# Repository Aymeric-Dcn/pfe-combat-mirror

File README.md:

# PFE Combat Mirror — boxer motion capture

*[Version française](README.fr.md)*

Final-year project at Polytech Montpellier (MEA), with the Biomedical Engineering department of CSULB, the Australian company [Combat Mirror](https://combatmirror.com/) and LAAS-CNRS (Gepetto team).

**Goal:** fit a boxing mirror with pressure sensors (impact strength and location), synchronize them with the boxer's joint kinematics measured by RGB cameras with [RT-COSMIK](https://github.com/Gepetto/rt-cosmik), then score the training session with a learned model (Transformer).

| Deliverable | Status (2026-11-20) |
|---|---|
| 1. RT-COSMIK setup | **Done.** Full pipeline with one webcam (detection, skeleton, biomechanical model, joint angles to CSV); real time at 30 fps on the Polytech Debian machine |
| 2. Mirror instrumentation | **In progress.** 4-sensor FlexiForce force plate prototype: corner module (3D), conditioning (schematic, simulations, breadboard-validated), Nucleo firmware and PC script working; sensors on order |
| 3. Synchronization + CSV | **In progress.** Camera side ready; force plate frames carry a 2 kHz sample counter; hardware camera trigger planned (Nucleo TIM1) |
| 4. Data processing (ML) | Not started |

The progress report (French, LaTeX + compiled PDF) is in [`docs/rapport/`](docs/rapport/).

## Layout

```
config/cam_params/intrinsics/   webcam calibration (format read by RT-COSMIK main)
rtcosmik/patches/               our changes to RT-COSMIK (git apply)
scripts/tests/                  webcam, YOLO engine, NLF skeleton, engine header checks
scripts/calibration/            intrinsic calibration (checkerboard on a screen) + recompute
scripts/analysis/               take quality check + skeleton overlay video
scripts/tools/                  RT-COSMIK main setup + export from the container
scripts/forceplate/             force plate acquisition, live view and calibration (PC)
docker/                         image built on top of cosmik-dev-container's
results/                        takes (csv, plots; videos stay out of git)
hardware/3d/                    force plate parts (OpenSCAD): corner module, 4-sensor test rig
hardware/simulation/            sensor conditioning simulation (ngspice)
hardware/electronics/           sensor conditioning schematic (KiCad)
hardware/firmware/              Nucleo F072RB acquisition firmware (4 sensors, 2 kHz)
docs/                           setup guide (EN/FR), progress report and calibration protocol (FR)
```

## Quick start

Environment: the Docker image from [cosmik-dev-container](https://github.com/MaximeSabbah/cosmik-dev-container) (CUDA 12.1, Ubuntu 22.04, ROS 2 Humble, torch 2.4.1) plus Gepetto's RT-COSMIK `main`. Full setup, Windows/WSL 2 notes and troubleshooting: [`docs/SETUP.md`](docs/SETUP.md).

```bash
# inside the container
git clone https://github.com/Aymeric-Dcn/pfe-combat-mirror.git /root/pfe-combat-mirror
bash /root/pfe-combat-mirror/scripts/tools/setup_rtcosmik_main.sh
cd ~/workspace/ros_ws/RT-COSMIK-main
export YOLO_VERBOSE=False
python3 scripts/python/core/run_pipeline.py --online --cameras 0
```

Stand still and fully visible until `Model calibration finished`, then press `q` and `Ctrl+C` to stop. Results go to `output/<no_trial>/`.

On a recorded take:

```bash
python3 /root/pfe-combat-mirror/scripts/analysis/analyze_take.py output/demo_03
bash    /root/pfe-combat-mirror/scripts/analysis/overlay_offsets.sh output/demo_03 "0 0.5 1 1.5 2"
```

## Force plate (prototype)

Four FlexiForce A201 sensors, one under each corner of a plate, give the impact force (sum) and location (centre of pressure).

```
FlexiForce -> op-amp conditioning (MCP6004, 3.3 V) -> RC filter 480 Hz -> Nucleo F072RB ADC (2 kHz) -> USB -> forceplate.py
```

| Part | Where |
|---|---|
| Corner module and 300 mm test rig (OpenSCAD, parametric) | [`hardware/3d/`](hardware/3d/) |
| Conditioning schematic (KiCad) and bench test sheets | [`hardware/electronics/`](hardware/electronics/) |
| Circuit simulations (ngspice) | [`hardware/simulation/`](hardware/simulation/) |
| Acquisition firmware (STM32CubeIDE, register level) | [`hardware/firmware/nucleo_acq/`](hardware/firmware/nucleo_acq/) |
| PC acquisition, live view and calibration | [`scripts/forceplate/`](scripts/forceplate/) |
| Calibration protocol (FR) | [`docs/protocole_etalonnage.md`](docs/protocole_etalonnage.md) |

Quick start: import `hardware/firmware/nucleo_acq` in STM32CubeIDE and flash it (Run), then:

```bash
pip install pyserial numpy matplotlib
cd scripts/forceplate
python forceplate.py -p COM4 monitor     # or /dev/ttyACM0; --sim to try without the board
python forceplate.py -p COM4 live
```

## Changes to RT-COSMIK

- `0001-nlf-import-torchvision.patch`: the NLF TorchScript model calls `torchvision::nms`, which is only registered once `torchvision` is imported. Without it the pipeline process crashes at startup.
- `0002-settings-single-webcam.patch`: 640x480 at 30 fps, one camera, `sbs` inverse kinematics, subject height and weight.

## References

- RT-COSMIK: https://github.com/Gepetto/rt-cosmik
- Camera calibration (LAAS): https://github.com/Gepetto/cams_calibration
- ROS 2 bridge: https://github.com/Gepetto/rtcosmik_ros
- Dev container: https://github.com/MaximeSabbah/cosmik-dev-container

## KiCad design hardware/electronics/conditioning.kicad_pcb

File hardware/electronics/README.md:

# Conditioning board (rev 3.1): 4-channel shield for the NUCLEO-F072RB

KiCad 10 project `conditioning`.
One MCP6004 conditions the 4 FlexiForce A201 sensors (V_OUT = V_REF x (1 + R_F / R_sensor)); the board plugs on the Arduino headers of the Nucleo.

## Connectors

| Ref | Function | Footprint |
|---|---|---|
| FS1-FS4 | FlexiForce sensors, plugged directly (outer pins active, centre pin unused) | 1x03 female socket, 2.54 mm |
| J1 | Nucleo CN6 (power): 3V3 and GND used | 1x08 male header |
| J2 | Nucleo CN8 (analog): A0-A3 sensors, A4 V_REF | 1x06 male header |
| J3 | Nucleo CN9 (digital): D7/PA8 camera trigger, D6/PB10 camera strobe; D0/D1 (ST-LINK UART) left free | 1x08 male header |
| J4 | Cameras: 1 trigger, 2 strobe, 3 GND | 1x03 male header |
| JP1 | Mode: 1-2 sensitive (1.03 V), 3-4 standard (0.51 V), 5-6 high force (0.10 V) | 2x03 header + jumper |
| JP2 | 3V3 from the Nucleo; remove the jumper to measure the current | 1x02 header + jumper |
| JP3-JP6 | Op-amp output to the RO/CO filter; remove to drive the filter from a generator | 1x02 header + jumper |

## Test points

Single header pins (1x01).

| Ref | Signal |
|---|---|
| TP1-TP4 | op-amp outputs (before RO) |
| TP5-TP8 | ADC inputs (after the RO/CO filter) |
| TP9 | V_REF |
| TP10 | 3V3 |
| TP11-TP14 | GND, one near each channel for the probe clips |

No test point on the inverting inputs: a probe there adds about 100 pF and makes the amplifier ring.

## Shield placement

The male headers are inserted from the component side and soldered on the copper side, so the board works single-sided.
Header positions, from the Arduino Uno R3 layout (pin centres, mm, origin on A0, x to the right, y towards the digital headers):

| Header | Pin 1 | Last pin | y |
|---|---|---|---|
| J2 (CN8) | A0: x = 0 | A5: x = 12.70 | 0 |
| J1 (CN6) | NC: x = -22.86 | VIN: x = -5.08 | 0 |
| J3 (CN9) | D0: x = 15.24 | D7: x = -2.54 | 48.26 |

Check these positions before etching: place the KiCad footprint `Module:Arduino_UNO_R3` on the PCB as a reference, or measure the Nucleo headers.

Height: the Nucleo with the shield fits between the plates of the test rig (47.75 mm gap); orient the corner modules so that the sensor tails point to the centre.

## Etching rules (Polytech machine, provisional)

Single-sided, no plated holes: tracks 0.6 mm minimum, clearance 0.5 mm, pads 2 mm minimum (2.5 mm for headers), 1.0 mm drills for headers, 0.8 mm for resistors and capacitors. To be confirmed with the technician.

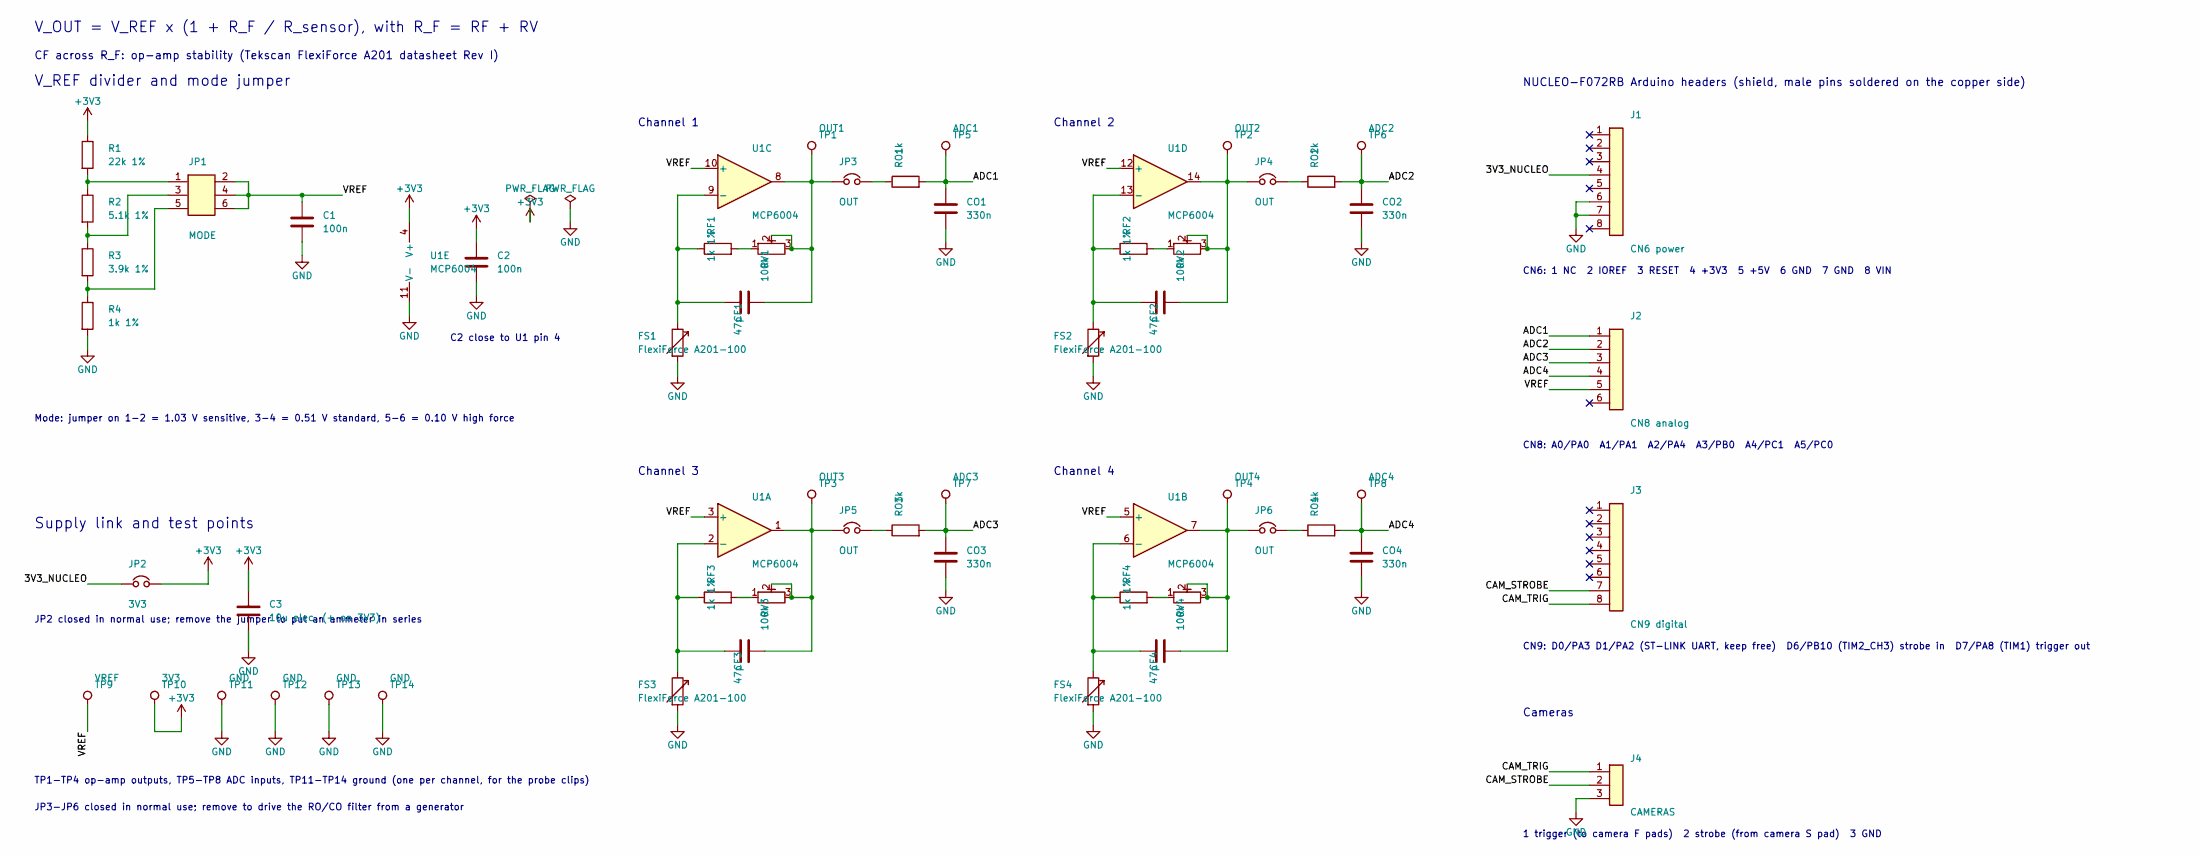
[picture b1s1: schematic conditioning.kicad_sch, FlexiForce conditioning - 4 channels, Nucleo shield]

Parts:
C1, C2: 100n; C_Disc_D5.0mm_W2.5mm_P2.50mm
C3: 10u elec. (+ on 3V3); CP_Radial_D5.0mm_P2.50mm
CF1, CF2, CF3, CF4: 47p; C_Disc_D5.0mm_W2.5mm_P2.50mm
CO1, CO2, CO3, CO4: 330n; C_Disc_D5.0mm_W2.5mm_P2.50mm
FS1, FS2, FS3, FS4: FlexiForce A201-100; PinSocket_1x03_P2.54mm_Vertical
J1: CN6 power; PinHeader_1x08_P2.54mm_Vertical
J2: CN8 analog; PinHeader_1x06_P2.54mm_Vertical
J3: CN9 digital; PinHeader_1x08_P2.54mm_Vertical
J4: CAMERAS; PinHeader_1x03_P2.54mm_Vertical
JP1: MODE; PinHeader_2x03_P2.54mm_Vertical
JP2: 3V3; PinHeader_1x02_P2.54mm_Vertical
JP3, JP4, JP5, JP6: OUT; PinHeader_1x02_P2.54mm_Vertical
R1: 22k 1%; R_Axial_DIN0207_L6.3mm_D2.5mm_P7.62mm_Horizontal
R2: 5.1k 1%; R_Axial_DIN0207_L6.3mm_D2.5mm_P7.62mm_Horizontal
R3: 3.9k 1%; R_Axial_DIN0207_L6.3mm_D2.5mm_P7.62mm_Horizontal
R4: 1k 1%; R_Axial_DIN0207_L6.3mm_D2.5mm_P7.62mm_Horizontal
RF1, RF2, RF3, RF4: 1k 1%; R_Axial_DIN0207_L6.3mm_D2.5mm_P7.62mm_Horizontal
RO1, RO2, RO3, RO4: 1k; R_Axial_DIN0207_L6.3mm_D2.5mm_P7.62mm_Horizontal
RV1, RV2, RV3, RV4: 100k; Potentiometer_Bourns_3296W_Vertical
TP1: OUT1; PinHeader_1x01_P2.54mm_Vertical
TP2: OUT2; PinHeader_1x01_P2.54mm_Vertical
TP3: OUT3; PinHeader_1x01_P2.54mm_Vertical
TP4: OUT4; PinHeader_1x01_P2.54mm_Vertical
TP5: ADC1; PinHeader_1x01_P2.54mm_Vertical
TP6: ADC2; PinHeader_1x01_P2.54mm_Vertical
TP7: ADC3; PinHeader_1x01_P2.54mm_Vertical
TP8: ADC4; PinHeader_1x01_P2.54mm_Vertical
TP9: VREF; PinHeader_1x01_P2.54mm_Vertical
TP10: 3V3; PinHeader_1x01_P2.54mm_Vertical
TP11, TP12, TP13, TP14: GND; PinHeader_1x01_P2.54mm_Vertical
U1: MCP6004; DIP-14_W7.62mm

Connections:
+3V3: C2.1, C3.1, JP2.2, R1.1, TP10.1, U1.4 (V+)
/3V3_NUCLEO: J1.4, JP2.1
/ADC1: CO1.1, J2.1, RO1.2, TP5.1
/ADC2: CO2.1, J2.2, RO2.2, TP6.1
/ADC3: CO3.1, J2.3, RO3.2, TP7.1
/ADC4: CO4.1, J2.4, RO4.2, TP8.1
/CAM_STROBE: J3.7, J4.2
/CAM_TRIG: J3.8, J4.1
/VREF: C1.1, J2.5, JP1.2, JP1.4, JP1.6, TP9.1, U1.3 (+), U1.5 (+), U1.10 (+), U1.12 (+)
GND: C1.2, C2.2, C3.2, CO1.2, CO2.2, CO3.2, CO4.2, FS1.3, FS2.3, FS3.3, FS4.3, J1.6, J1.7, J4.3, R4.2, TP11.1, TP12.1, TP13.1, TP14.1, U1.11 (V-)
unnamed: CF1.2, JP3.1, RV1.2, RV1.3, TP1.1, U1.8
unnamed: CF2.2, JP4.1, RV2.2, RV2.3, TP2.1, U1.14
unnamed: CF3.2, JP5.1, RV3.2, RV3.3, TP3.1, U1.1
unnamed: CF4.2, JP6.1, RV4.2, RV4.3, TP4.1, U1.7
unnamed: JP1.1, R1.2, R2.1
unnamed: JP1.3, R2.2, R3.1
unnamed: JP1.5, R3.2, R4.1
unnamed: JP3.2, RO1.1
unnamed: JP4.2, RO2.1
unnamed: JP5.2, RO3.1
unnamed: JP6.2, RO4.1
unnamed: RF1.2, RV1.1
unnamed: RF2.2, RV2.1
unnamed: RF3.2, RV3.1
unnamed: RF4.2, RV4.1
unnamed: CF1.1, FS1.1, RF1.1, U1.9 (-)
unnamed: CF2.1, FS2.1, RF2.1, U1.13 (-)
unnamed: CF3.1, FS3.1, RF3.1, U1.2 (-)
unnamed: CF4.1, FS4.1, RF4.1, U1.6 (-)

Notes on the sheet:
V_REF divider and mode jumper
Mode: jumper on 1-2 = 1.03 V sensitive, 3-4 = 0.51 V standard, 5-6 = 0.10 V high force
C2 close to U1 pin 4
Channel 1
Channel 2
Channel 3
Channel 4
NUCLEO-F072RB Arduino headers (shield, male pins soldered on the copper side)
CN6: 1 NC 2 IOREF 3 RESET 4 +3V3 5 +5V 6 GND 7 GND 8 VIN
CN8: A0/PA0 A1/PA1 A2/PA4 A3/PB0 A4/PC1 A5/PC0
CN9: D0/PA3 D1/PA2 (ST-LINK UART, keep free) D6/PB10 (TIM2_CH3) strobe in D7/PA8 (TIM1) trigger out
Cameras
1 trigger (to camera F pads) 2 strobe (from camera S pad) 3 GND
Supply link and test points
JP2 closed in normal use; remove the jumper to put an ammeter in series
TP1-TP4 op-amp outputs, TP5-TP8 ADC inputs, TP11-TP14 ground (one per channel, for the probe clips)
JP3-JP6 closed in normal use; remove to drive the RO/CO filter from a generator
V_OUT = V_REF x (1 + R_F / R_sensor), with R_F = RF + RV
CF across R_F: op-amp stability (Tekscan FlexiForce A201 datasheet Rev I)

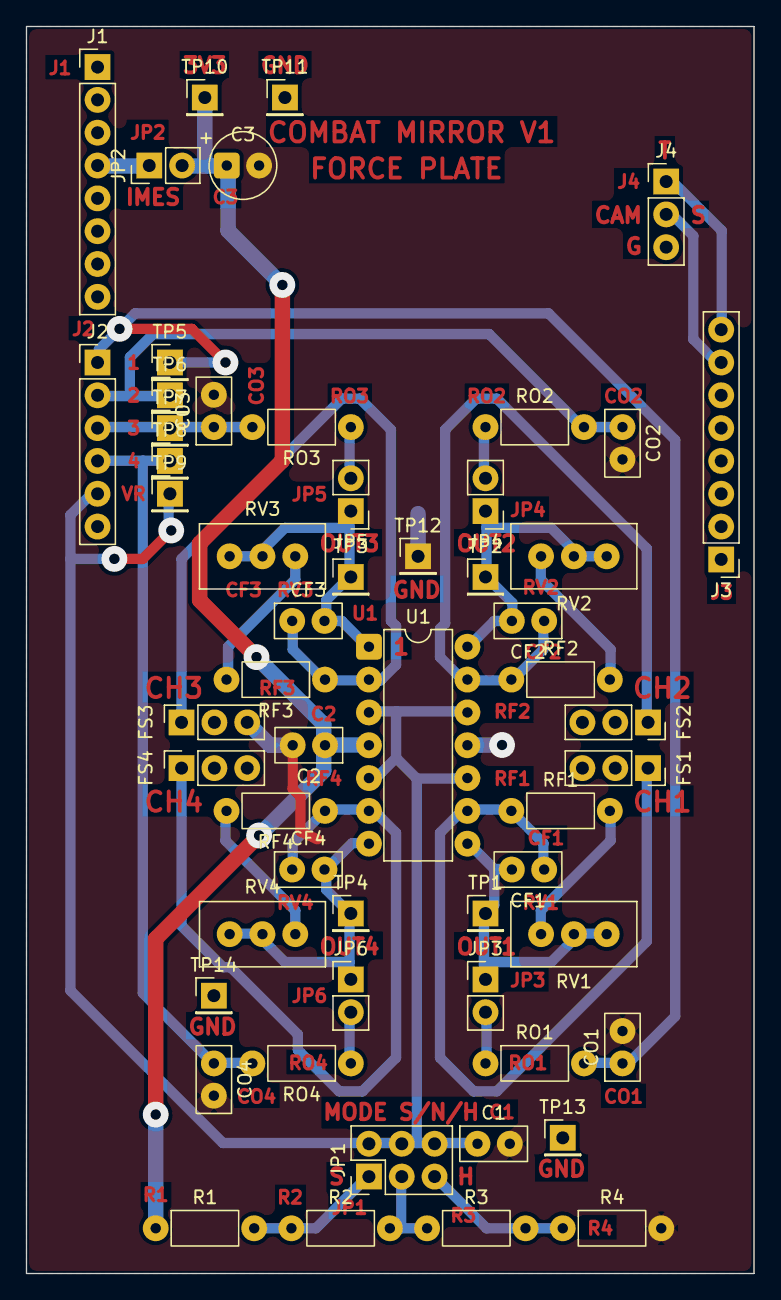
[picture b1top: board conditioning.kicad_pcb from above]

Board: 2 copper layers, 56.3 x 96.5 mm, 56 parts (0 on the bottom side), 29 nets.
